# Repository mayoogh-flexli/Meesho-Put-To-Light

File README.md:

# PTL-RAIL — Meesho Put-To-Light IR Rail

Modular, daisy-chained **5-node IR emitter/receiver rail** for the Meesho
put-to-light system. Each 400 mm board has five bin positions on an 84 mm pitch.
Each position has an IR LED firing out of the top edge into the bin above and a
TSOP IR receiver looking out of the bottom edge into the bin below. An onboard
**ESP32-S3** drives the emitters, reads its own receivers and the receivers of
the board above, and talks to the rest of the system over **CAN**. Power, CAN
and the receiver signals pass from board to board through screw terminals.

| | |
|---|---|
| **Board** | PTL-RAIL |
| **Revision** | rev A (v1.0) |
| **Status** | Released as [`ptl-rail-rev-a-v1.0`](../../releases/tag/ptl-rail-rev-a-v1.0). ERC/DRC clean; see [§14](#14-known-issues-rev-a) for open items |
| **EDA** | KiCad 10 |
| **License** | Private / Internal (Flexli Technologies) |

---

## 1. Overview

One board type, chained end to end along a rack:

- **IR emitter row (top edge):** 5× IR333C 5 mm IR LEDs (D7–D11), mounted horizontally so the lens points out of the top edge. Each LED is switched by an AO3400A low-side MOSFET (Q1–Q5) from an ESP32 GPIO (`TX_1`…`TX_5`).
- **IR receiver row (bottom edge):** 5× TSOP382xx (U6–U10), lens pointing out of the bottom edge. Their outputs (`TSOP_OUT_1`…`5`) leave on **J3** to the board below. The receivers of the board above arrive on **J4** (`TSOP_OUT_n_ESP`) and go into the ESP32.
- **3D-printed shrouds:** each LED and each TSOP sits under a printed shroud (28 mm silk outline), held by two M3 screws, which reduces reflections and narrows the field of view.
- **Controller:** ESP32-S3-WROOM-1 (native USB through J1, onboard antenna overhanging the top edge), WS2812B status LEDs, RST/BOOT buttons and a user ACK button.
- **Bus and power:** CAN via SN65HVD230 with PESD1CAN ESD and switchable 120 Ω termination. VIN (24 V nominal) → TPS54360B buck → +5 V → TLV1117-33 → +3V3.

---

## 2. Architecture Block Diagram

```mermaid
flowchart TB
    subgraph PWR["Power"]
        VIN[("VIN 24 V nominal\nJ3/J4/J5/J6")] --> BUCK["TPS54360B buck\n(L1 15 uH, D1 SS36) -> +5V"]
        BUCK --> LDO["TLV1117-33\nLDO -> +3V3"]
        USB[("J1 USB 5V")] -->|"D3 SS14"| BUCK5(("+5V"))
    end

    subgraph MCU["Controller"]
        ESP["ESP32-S3-WROOM-1"]
        CAN["SN65HVD230 + PESD1CAN\nSW3 120R termination"]
        RGB["WS2812B x3 (D4-D6)"]
        ESP -->|"IO15/IO16"| CAN
        ESP -->|"IO18"| RGB
    end

    subgraph NODES["5 nodes, 84 mm pitch"]
        TX["5x IR333C + AO3400A\n(top edge)"]
        RX["5x TSOP382xx\n(bottom edge)"]
    end

    ESP -->|"TX_1-5 (IO9-IO13)"| TX
    RX -->|"TSOP_OUT_1-5 -> J3"| BELOW(["board below"])
    ABOVE(["board above"]) -->|"J4 -> IO4-IO8"| ESP
    CAN <-->|"CAN_H/CAN_L\nJ5/J6, J3/J4"| BUS(["CAN bus"])
```

---

## 3. Board Snapshots

### Top

### Bottom (node passives and MOSFETs)

### Node 2, ESP32, USB and CAN close-up

---

## 4. Features

| | |
|---|---|
| Board | 400 × 40 mm, 2-layer FR-4, 1.6 mm. 4 mm corner radius, concentric with the corner holes |
| Nodes | 5. Centres at x = 32, 116, 200, 284, 368 mm from the left edge |
| Emitters | IR333C, 180 Ω from +5 V, AO3400A low-side switch, 100 Ω gate resistor and 100 kΩ pull-down |
| Receivers | TSOP382xx on +3V3 through 100 Ω + 4.7 µF, 100 Ω series resistor on the output |
| Controller | ESP32-S3-WROOM-1, native USB (USBLC6-2 ESD) on J1 |
| Bus | CAN, SN65HVD230, PESD1CAN, switchable 120 Ω termination (SW3 + R7) |
| User I/O | SW1 RST, SW2 BOOT, SW4 ACK_BUTTON (IO14, 10 kΩ pull-up, 100 nF), D2 power LED, D4–D6 WS2812B |
| Copper | GND pour on both layers, redundant GND vias, GND via fence along the board edge |
| Test | TP1–TP19 (loop test points on every TX/RX signal and every rail, see [§10](#10-test-points)) |

---

## 5. Absolute Maximum Ratings

Stress ratings come from the component datasheets. **Rev A has no input protection** (see [§14](#14-known-issues-rev-a)), so these are the limits of the silicon itself.

| Parameter | Limiting part | Min | Max | Unit |
|---|---|---:|---:|---|
| `VIN` | TPS54360B (U2) | −0.3 | 65 | V |
| `VIN` on C1/C3 | capacitor rating, not yet specified | — | rating TBD | V |
| CAN_H / CAN_L bus pins | SN65HVD230 (U5) | −4 | 16 | V |
| +3V3 rail | ESP32-S3 / TLV1117 output | −0.3 | 3.6 | V |
| +5V rail | USBLC6-2 VBUS (U4) | −0.3 | 5.5 | V |

## 6. Recommended Operating Conditions

| Parameter | Min | Typ | Max | Unit |
|---|---:|---:|---:|---|
| `VIN` | 4.5 (U2) | 24 | 60 (U2), subject to C1/C3 rating | V |
| CAN data rate | — | — | 1 | Mbps |

---

## 7. System Wiring Diagram

```mermaid
flowchart TB
    A["Rail board N-1 (above)"] -->|"J3 -> J4\nTSOP_OUT 1-5, CAN, VIN, GND"| B["Rail board N"]
    B -->|"J3 -> J4"| C["Rail board N+1 (below)"]
    L(["neighbour on the left"]) <-->|"J5: CAN_H, CAN_L, VIN, GND"| B
    B <-->|"J6: GND, VIN, CAN_L, CAN_H"| R(["neighbour on the right"])
```

J3 carries this board's receiver outputs down to the next board's J4, which
feeds that board's ESP32 IO4–IO8. J3/J4 also pass CAN and power. J5/J6 at the
two ends of the board are mirrored 4-way CAN + power terminals for chaining
along the rail. The J3 → J4 pin order is reversed (J3.1 = RX1, J4.10 = RX1), so
**check the harness before first power-up**.

---

## 8. Connector Reference

Pin labels are printed on both silkscreen sides.

| Connector | Type | Pinout (1→N) |
|---|---|---|
| `J3` TSOP OUT | 10-way 3.5 mm screw terminal | 1–5: `RX1`…`RX5` (TSOP_OUT_1…5) · 6: `CAN_H` · 7: `CAN_L` · 8: `VIN` · 9: `GND` · 10: `GND` |
| `J4` TSOP IN | 10-way 3.5 mm screw terminal | 1: `GND` · 2: `GND` · 3: `VIN` · 4: `CAN_L` · 5: `CAN_H` · 6–10: `RX5`…`RX1` (TSOP_OUT_5…1_ESP) |
| `J5` (left end) | 4-way 3.5 mm screw terminal | 1: `CAN_H` · 2: `CAN_L` · 3: `VIN` · 4: `GND` |
| `J6` (right end) | 4-way 3.5 mm screw terminal | 1: `GND` · 2: `VIN` · 3: `CAN_L` · 4: `CAN_H` |
| `J1` USB | JST-PH 4-way | 1: `GND` · 2: `D+` · 3: `D−` · 4: `5V` (VBUS, via D3) |
| `SW3` | slide DIP | ON = 120 Ω (R7) across CAN_H/CAN_L |

---

## 9. ESP32-S3-WROOM-1 Pin Allocation

| Pin # | Pin name | Net / function |
|---:|---|---|
| 1 | `GND` | Ground |
| 2 | `3V3` | 3.3 V supply |
| 3 | `EN` | `ESP_EN`, reset (SW1) |
| 4 | `IO4` | `TSOP_OUT_1_ESP` (J4.10) |
| 5 | `IO5` | `TSOP_OUT_2_ESP` (J4.9) |
| 6 | `IO6` | `TSOP_OUT_3_ESP` (J4.8) |
| 7 | `IO7` | `TSOP_OUT_4_ESP` (J4.7) |
| 8 | `IO15` | `CAN_TX` |
| 9 | `IO16` | `CAN_RX` |
| 10 | `IO17` | *unused* |
| 11 | `IO18` | `STATUS_LED` (WS2812B DIN, D4→D5→D6) |
| 12 | `IO8` | `TSOP_OUT_5_ESP` (J4.6) |
| 13 | `IO19` | `USB_D-` |
| 14 | `IO20` | `USB_D+` |
| 15 | `IO3` | *unused (strap pin)* |
| 16 | `IO46` | *unused (strap pin)* |
| 17 | `IO9` | `TX_1` (emitter node 1) |
| 18 | `IO10` | `TX_2` |
| 19 | `IO11` | `TX_3` |
| 20 | `IO12` | `TX_4` |
| 21 | `IO13` | `TX_5` |
| 22 | `IO14` | `ACK_BUTTON` (SW4) |
| 23–25 | `IO21`, `IO47`, `IO48` | *unused* |
| 26 | `IO45` | *unused, no-connect (VDD_SPI strap; keep low at boot)* |
| 27 | `IO0` | `GPIO0`, BOOT (SW2) |
| 28–35 | `IO35`–`IO42` | *unused* |
| 36, 37 | `RXD0`, `TXD0` | *unused (UART0 debug)* |
| 38, 39 | `IO2`, `IO1` | *unused (ADC-capable)* |
| 40, 41 | `GND` | Ground / thermal pad |

---

## 10. Test Points

| TP | Net | Footprint |
|---|---|---|
| TP1 / TP2 | `USBC_D+` / `USBC_D−` (connector side) | SMD pad Ø1.5 mm |
| TP3 / TP4 | `USB_D+` / `USB_D−` (ESP32 side) | SMD pad Ø1.5 mm |
| TP5 … TP9 | `TX_1` … `TX_5` | Loop Ø1.8 mm, drill 1.0 mm |
| TP10 … TP14 | `TSOP_OUT_1` … `TSOP_OUT_5` | Loop Ø1.8 mm, drill 1.0 mm |
| TP15 / TP16 / TP17 | `VIN` / `+5V` / `+3V3` | Loop Ø1.8 mm, drill 1.0 mm |
| TP18 / TP19 | `GND` | Loop Ø1.8 mm, drill 1.0 mm |

---

## 11. Mounting & IR Shrouds

- **Rail fixing:** H1–H4 (corners, M3 with plated pad, 4 mm from each edge) and H25–H28 (mid-board, M3 with plated pad).
- **Shroud fixing:** H5–H24 are NPTH Ø3.2 mm, at each node centre ±10 mm, 5.0 mm (LED side) and 35.0 mm (TSOP side) from the top edge. The 28 mm silk outlines show each shroud's footprint; no parts are placed inside them.
- **Antenna:** the ESP32 antenna overhangs the top edge by about 15 mm. Keep the rack upright and any metal clear of it.

---

## 12. Fabrication & Assembly

**Fabrication**
- 2-layer FR-4, 1.6 mm. Copper weight and surface finish are not specified in the design; 1 oz and HASL-LF or ENIG are suitable.
- Design rules: min track 0.2 mm, clearance 0.2 mm, via 0.6/0.3 mm, min hole 0.3 mm, copper-to-edge 0.5 mm, hole-to-hole 0.25 mm.
- U3's thermal-pad vias use 0.2 mm holes, below the 0.3 mm design rule. Confirm your fab can make them.
- **Panel:** 2-up, 400 × 127 mm. Board 2 is rotated 180° so both antenna overhangs land on the 20 mm top/bottom rails. Each long edge has 7 mouse-bite tabs (Ø0.5 mm, 0.8 mm pitch, 3 mm wide), placed clear of the LEDs, TSOPs, connectors and antenna. The rails carry 3 fiducials and 3 tooling holes.

**Assembly**
- **Top:** ESP32, power stage, CAN, WS2812Bs, switches, connectors, IR LEDs, TSOPs.
- **Bottom:** all node passives and MOSFETs (R9–R33, C22–C26, Q1–Q5).
- **Through-hole:** IR LEDs, TSOPs, screw terminals, J1, SW3 and the loop test points.

---

## 13. Releases

The production files are attached to each [GitHub release](../../releases). The current release is [`ptl-rail-rev-a-v1.0`](../../releases/tag/ptl-rail-rev-a-v1.0):

| Asset | File |
|---|---|
| Bill of Materials | `PTL-RAIL_revA_BOM.csv` (grouped by Value + Footprint; test points and holes excluded) |
| Gerbers + drill files (fabrication, 2-board panel) | `PTL-RAIL_revA_gerbers_drill_panel-2up.zip` (with panel pick-and-place in `assembly/`) |
| Interactive BOM | `PTL-RAIL_revA_ibom.html` |
| IPC netlist | `PTL-RAIL_revA_netlist.ipc` (IPC-D-356) |
| Pick-and-place position file | `PTL-RAIL_revA_pick-and-place.csv` (single board, both sides, mm) |
| Reference designator list | `PTL-RAIL_revA_refdes.csv` |
| Schematic (PDF plot) | `PTL-RAIL_revA_schematic.pdf` |
| Schematic (KiCad source) | `PTL-RAIL_revA_kicad-source.zip` (project, sheets, PCB, libraries, 3D models, panel PCB) |
| 3D model (STEP) | `PTL-RAIL_revA_step.zip` → `PTL-RAIL_revA.step` (board, components, copper, silkscreen; ~40 MB unzipped) |

### Repository layout

```
.
├── README.md                      This file
└── PTL-RAIL/
    ├── PTL-RAIL.kicad_pro         KiCad project
    ├── PTL-RAIL.kicad_sch         Root sheet
    ├── PTL-RAIL.kicad_pcb         Board layout
    ├── esp32.kicad_sch            ESP32-S3, USB, buttons, status LEDs, test points
    ├── power.kicad_sch            TPS54360B buck, TLV1117 LDO
    ├── can.kicad_sch              SN65HVD230 CAN interface
    ├── connectors.kicad_sch       J3/J4/J5/J6
    ├── tx_nodes.kicad_sch         5x IR emitter + MOSFET
    ├── rx_nodes.kicad_sch         5x TSOP receiver
    ├── lib/                       Project symbols, footprints (0_IC) and 3D models
    └── Docs/
        ├── datasheets/            Component datasheets
        └── renders/               Board renders used in this README
```

---

## 14. Known Issues (rev A)

1. **No 24 V input protection.** VIN goes straight to C1/C3 and U2: no fuse, reverse-polarity protection, TVS or bulk capacitor.
2. **CAN_L sits next to VIN** on J3 (7/8), J4 (3/4), J5 (2/3) and J6 (2/3). The SN65HVD230 bus pins are rated −4 … +16 V, so a 24 V short destroys the transceiver. Either separate the pins with GND or use a ±58/70 V part (e.g. TCAN1042, MCP2562FD).
3. **J3/J4 pin order is reversed.** Check the board-to-board harness.
4. **J4 inputs are unprotected.** IO4–IO8 connect straight to an off-board connector with no series resistor, pull-up, RC filter or ESD protection.
5. **WS2812B data level.** It is driven at 3.3 V while the LEDs run on 5 V (V_IH = 0.7 × VDD), which is marginal.
6. **No capacitor voltage ratings or MPNs.** C1/C3 sit on 24 V and need ≥ 50 V.
7. **U3 overlaps the node-3 emitter shroud and hole H19** (DRC exclusion set).
8. **J3–J6 3D models** are a Phoenix PT 3.5 mm stand-in (KiCad has no 4Ucon models). This affects renders only.

---

## 15. Revision History

| Revision | Date | Notes |
|---|---|---|
| rev A scaffold | 2026-10-17 | KiCad project skeleton: outline, holes, node markers, sheets. |
| rev A placement | 2026-10-17 | LED row on the top edge, TSOP row on the bottom edge, node parts at 84 mm pitch, J3/J4 10-way and J5/J6 4-way terminals, CAN block, buttons, status LEDs, mounting holes. |
| rev A layout | 2026-10-18 | IR shroud outlines and holes, node parts moved to the bottom side, routing with filleted bus, GND vias and edge via fence, silkscreen cleanup, mid-board holes, rounded corners, test points TP5–TP19, SW4 ACK button on IO14. |
| **rev A v1.0** | 2026-10-18 | Values normalised, ERC/DRC clean, 3D models, production files and release [`ptl-rail-rev-a-v1.0`](../../releases/tag/ptl-rail-rev-a-v1.0). |

---

© Flexli Technologies. Private / internal.

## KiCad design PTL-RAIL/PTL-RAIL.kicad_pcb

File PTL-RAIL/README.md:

# PTL-RAIL — modular IR TX/RX rail, rev A

KiCad 10 project for the Meesho put-to-light rail. One board carries five IR
emitter/receiver nodes, an ESP32-S3 controller and a CAN interface. Boards
daisy-chain through screw terminals.

| | |
|---|---|
| Board size | 400 × 40 mm, 4 mm corner radius (concentric with the corner holes) |
| Layers | 2 (F.Cu / B.Cu), 1.6 mm, GND pour on both layers with edge via fence |
| Nodes | 5, on an 84 mm pitch (centres at x = 32, 116, 200, 284, 368 mm from the left edge) |
| Controller | ESP32-S3-WROOM-1 (U3, onboard antenna, overhangs the top edge) |
| Bus | CAN, SN65HVD230 (U5) with PESD1CAN (CR1) and switchable 120 Ω termination (SW3 + R7) |
| Power | VIN (24 V nominal) → TPS54360B buck (U2, L1 15 µH, D1 SS36) → +5 V → TLV1117-33 (U1) → +3V3 |
| USB | J1 JST-PH 4-pin (5 V via D3 SS14, USBLC6-2 ESD on D+/D−) |

## Block overview

- **IR emitter row (top edge):** D7–D11 IR333C, 5 mm, mounted horizontally and firing out of the top edge. Each LED is switched by an AO3400A low-side MOSFET (Q1–Q5) with a 100 Ω gate resistor, a 100 kΩ gate pull-down and a 180 Ω LED resistor from +5 V.
- **IR receiver row (bottom edge):** U6–U10 TSOP382xx, lens facing out of the bottom edge. Each has a 100 Ω supply resistor and 4.7 µF on Vs (+3V3), plus a 100 Ω series resistor on the output.
- **Shrouds:** each emitter and each TSOP sits under a 3D-printed shroud (28 mm silk outline). Each shroud is held by two M3 screws at the node centre ±10 mm, which reduces reflections and narrows the field of view.
- **Status:** D4–D6 WS2812B chain on IO18; D2 power LED.
- **User inputs:** SW1 = RST (EN), SW2 = BOOT (IO0), SW4 = ACK_BUTTON (IO14, 10 kΩ pull-up R34, 100 nF C27).

## Connector pinouts

Pin labels are printed on both silkscreen sides.

**J3 — 10-way, TSOP OUT (towards the board below)**

| Pin | 1 | 2 | 3 | 4 | 5 | 6 | 7 | 8 | 9 | 10 |
|---|---|---|---|---|---|---|---|---|---|---|
| Signal | RX1 | RX2 | RX3 | RX4 | RX5 | CAN_H | CAN_L | VIN | GND | GND |

**J4 — 10-way, TSOP IN (from the board above, into the ESP32)**

| Pin | 1 | 2 | 3 | 4 | 5 | 6 | 7 | 8 | 9 | 10 |
|---|---|---|---|---|---|---|---|---|---|---|
| Signal | GND | GND | VIN | CAN_L | CAN_H | RX5 | RX4 | RX3 | RX2 | RX1 |

On J3, RXn is this board's TSOP output (TSOP_OUT_n). On J4, RXn is TSOP_OUT_n_ESP.

**J5 (left end) / J6 (right end) — 4-way CAN + power, mirrored**

| Pin | 1 | 2 | 3 | 4 |
|---|---|---|---|---|
| J5 | CAN_H | CAN_L | VIN | GND |
| J6 | GND | VIN | CAN_L | CAN_H |

**J1 — JST-PH 4-way USB:** 1 GND, 2 D+, 3 D−, 4 5 V (VBUS, via D3).

## ESP32-S3 pin map (U3)

| Function | GPIO | Module pin |
|---|---|---|
| TX_1 … TX_5 (emitter gates) | IO9 … IO13 | 17 … 21 |
| TSOP_OUT_1 … 5 _ESP (from J4) | IO4, IO5, IO6, IO7, IO8 | 4, 5, 6, 7, 12 |
| CAN_TX / CAN_RX | IO15 / IO16 | 8 / 9 |
| STATUS_LED (WS2812B DIN) | IO18 | 11 |
| ACK_BUTTON (SW4) | IO14 | 22 |
| USB D− / D+ | IO19 / IO20 | 13 / 14 |
| BOOT (SW2) | IO0 | 27 |
| EN (SW1) | EN | 3 |

All other GPIOs are unconnected. IO45 has a no-connect flag.

## Test points

| TP | Net | Footprint |
|---|---|---|
| TP1 / TP2 | USBC_D+ / USBC_D− (connector side) | Pad Ø1.5 mm |
| TP3 / TP4 | USB_D+ / USB_D− (ESP32 side) | Pad Ø1.5 mm |
| TP5 … TP9 | TX_1 … TX_5 | Loop Ø1.8 mm, drill 1.0 mm |
| TP10 … TP14 | TSOP_OUT_1 … TSOP_OUT_5 | Loop Ø1.8 mm, drill 1.0 mm |
| TP15 / TP16 / TP17 | VIN / +5V / +3V3 | Loop Ø1.8 mm, drill 1.0 mm |
| TP18 / TP19 | GND | Loop Ø1.8 mm, drill 1.0 mm |

## Mounting

- **Rail fixing:** H1–H4 (corners, M3 with plated pad, 4 mm from each edge), plus H25–H28 mid-board (M3 with plated pad).
- **Shroud fixing:** H5–H24 are NPTH Ø3.2 mm. They sit at each node centre ±10 mm, at y = 5.0 mm (LED side) and 35.0 mm (TSOP side) from the top edge.
- **Antenna:** the ESP32 antenna overhangs the top edge. Keep the rack upright and any metal clear of it.

## Fabrication notes

- 2-layer FR-4, 1.6 mm. Copper weight and surface finish are not specified in the design; 1 oz and HASL-LF or ENIG are suitable.
- Design rules: min track 0.2 mm, min clearance 0.2 mm, via 0.6 mm / 0.3 mm drill, min hole 0.3 mm, copper-to-edge 0.5 mm, hole-to-hole 0.25 mm.
- Some footprints (the U3 thermal pad vias) use 0.2 mm holes, below the 0.3 mm design minimum. That DRC check is set to ignore, so confirm your fab supports it.
- **Panel:** 2-up, 400 × 127 mm. Board 2 is rotated 180° so both antenna overhangs land on the 20 mm top/bottom rails. Boards are joined by 7 mouse-bite tabs per long edge (Ø0.5 mm, 0.8 mm pitch, 3 mm wide), placed clear of the LEDs, TSOPs, connectors and antenna. The rails carry 3 fiducials and 3 tooling holes.

## Assembly notes

- **Top side:** ESP32, power stage, CAN, WS2812s, switches, connectors, IR LEDs and TSOPs.
- **Bottom side:** all node passives and MOSFETs (R9–R33, C22–C26, Q1–Q5).
- **Through-hole:** IR LEDs, TSOPs, screw terminals, J1, SW3 and the loop test points.

## Production files (release assets)

| File | Content |
|---|---|
| `PTL-RAIL_revA_BOM.csv` | BOM grouped by Value + Footprint (test points and holes excluded) |
| `PTL-RAIL_revA_gerbers_drill_panel-2up.zip` | Gerbers, Excellon drill (PTH/NPTH) and drill maps for the 2-up panel, plus `assembly/` panel pick-and-place |
| `PTL-RAIL_revA_ibom.html` | Interactive HTML BOM |
| `PTL-RAIL_revA_netlist.ipc` | IPC-D-356 netlist for bare-board test |
| `PTL-RAIL_revA_pick-and-place.csv` | Single-board pick-and-place, both sides, mm |
| `PTL-RAIL_revA_refdes.csv` | Reference designator list (value, footprint, side, X/Y, rotation) |
| `PTL-RAIL_revA_schematic.pdf` | Schematic, all sheets |
| `PTL-RAIL_revA_kicad-source.zip` | KiCad project, schematics, PCB, local libraries and the panel PCB |

## Known open issues (rev A)

1. **No 24 V input protection.** VIN goes straight to C1/C3 and U2: no fuse, reverse-polarity protection, TVS or bulk capacitor.
2. **CAN_L sits next to VIN** on J3 (7/8), J4 (3/4), J5 (2/3) and J6 (2/3). The SN65HVD230 bus pins are rated −4 … +16 V, so a 24 V short destroys the transceiver. Either separate the pins with GND or use a ±58/70 V part (e.g. TCAN1042, MCP2562FD).
3. **J3/J4 pin order is reversed** (J3.1 = RX1, J4.10 = RX1). Check the harness wiring between boards.
4. **J4 inputs are unprotected.** IO4–IO8 connect straight to an off-board connector with no series resistor, pull-up, RC filter or ESD protection.
5. **WS2812B data level.** It is driven at 3.3 V while the LEDs run on 5 V (V_IH = 0.7 × VDD), which is marginal. Add a level shifter or a diode drop on the LED supply.
6. **No capacitor voltage ratings.** C1/C3 (on 24 V) need ≥ 50 V. No MPNs are assigned yet.
7. **U3 overlaps the node-3 emitter shroud and hole H19** (DRC exclusion set). The shroud screw lands near the module corner.

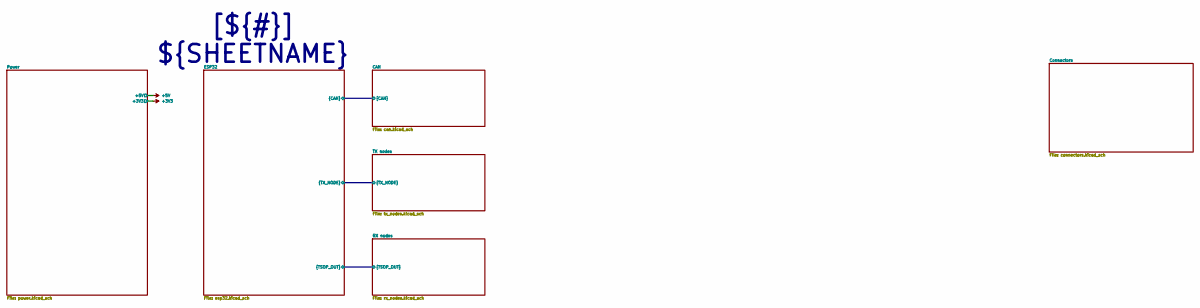
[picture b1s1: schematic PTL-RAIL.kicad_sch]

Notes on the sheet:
[${#}] ${SHEETNAME}

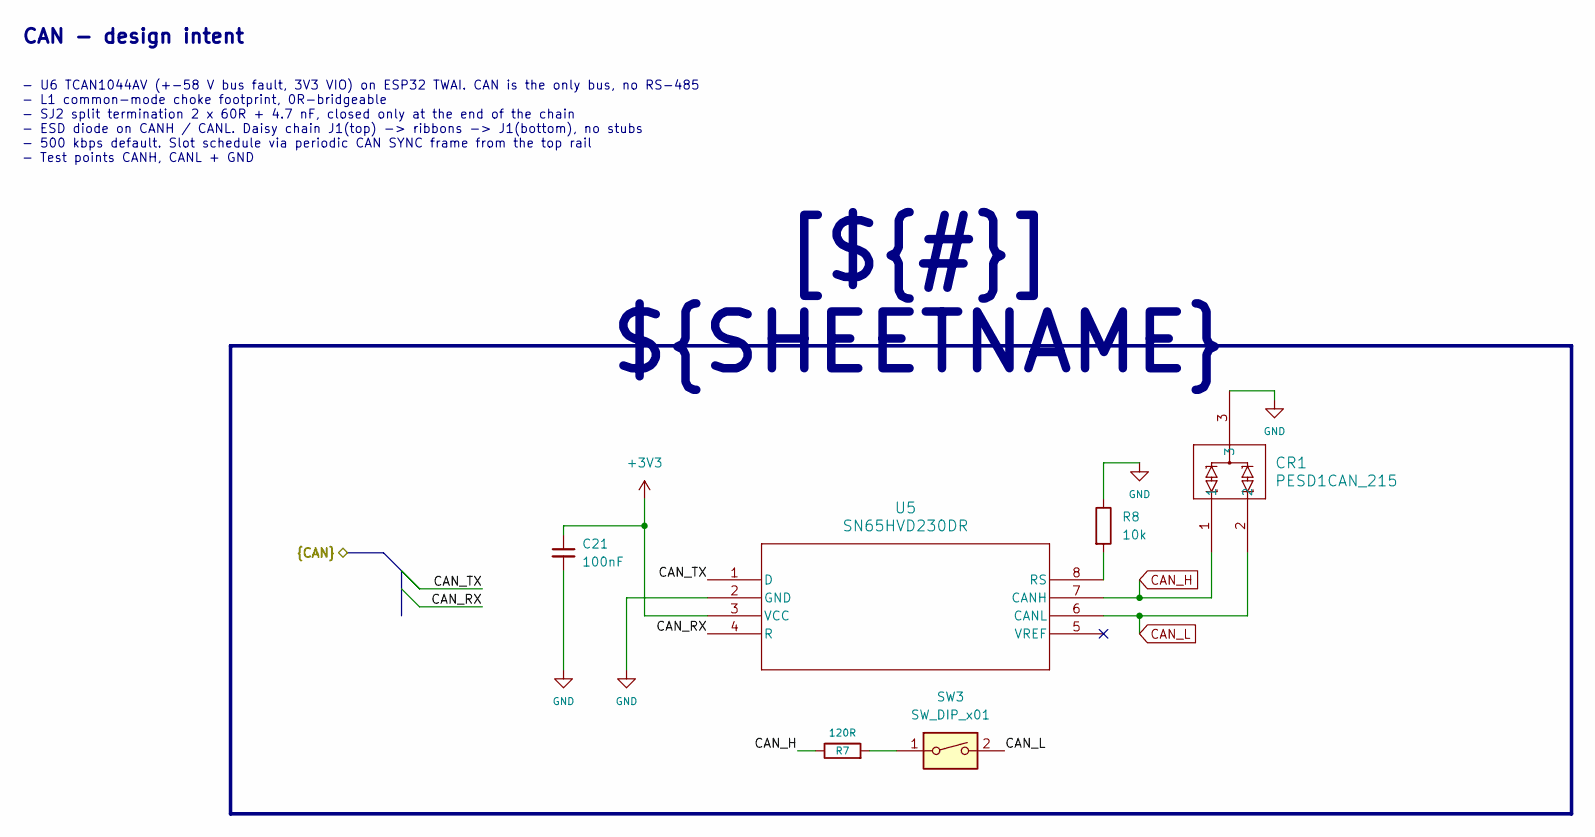
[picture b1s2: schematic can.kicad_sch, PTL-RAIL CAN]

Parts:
C21: 100nF; C_0805_2012Metric
CR1: PESD1CAN_215; SOT-23
R7: 120R; R_0805_2012Metric
R8: 10k; R_0805_2012Metric
SW3: SW_DIP_x01; SW_DIP_SPSTx01_Slide_9.78x4.72mm_W7.62mm_P2.54mm
U5: SN65HVD230DR; SOIC-8_3.9x4.9mm_P1.27mm

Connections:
+3V3: C21.1, U5.3 (VCC); also elsewhere on the board
/CAN/CAN_RX: U5.4 (R); also elsewhere on the board
/CAN/CAN_TX: U5.1 (D); also elsewhere on the board
CAN_H: CR1.1, R7.1, U5.7 (CANH); also elsewhere on the board
CAN_L: CR1.2, SW3.2, U5.6 (CANL); also elsewhere on the board
GND: C21.2, CR1.3, R8.1, U5.2 (GND); also elsewhere on the board
unnamed: R7.2, SW3.1
unnamed: R8.2, U5.8 (RS)

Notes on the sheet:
CAN - design intent
- U6 TCAN1044AV (+-58 V bus fault, 3V3 VIO) on ESP32 TWAI. CAN is the only bus, no RS-485 - L1 common-mode choke footprint, 0R-bridgeable - SJ2 split termination 2 x 60R + 4.7 nF, closed only at the end of the chain - ESD diode on CANH / CANL. Daisy chain J1(top) -> ribbons -> J1(bottom), no stubs 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
[${#}] ${SHEETNAME}

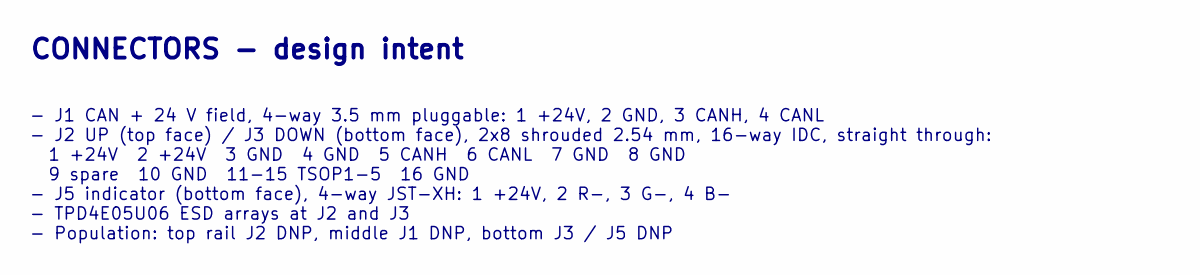
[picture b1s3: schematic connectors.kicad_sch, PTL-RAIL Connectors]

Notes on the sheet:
CONNECTORS - design intent
- J1 CAN + 24 V field, 4-way 3.5 mm pluggable: 1 +24V, 2 GND, 3 CANH, 4 CANL - J2 UP (top face) / J3 DOWN (bottom face), 2x8 shrouded 2.54 mm, 16-way IDC, straight through: 1 +24V 2 +24V 3 GND 4 GND 5 CANH 6 CANL 7 GND 8 GND 9 spare 10 GND 11-15 TSOP1-5 16 GND - J5 indicator (bottom face), 4-way JS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

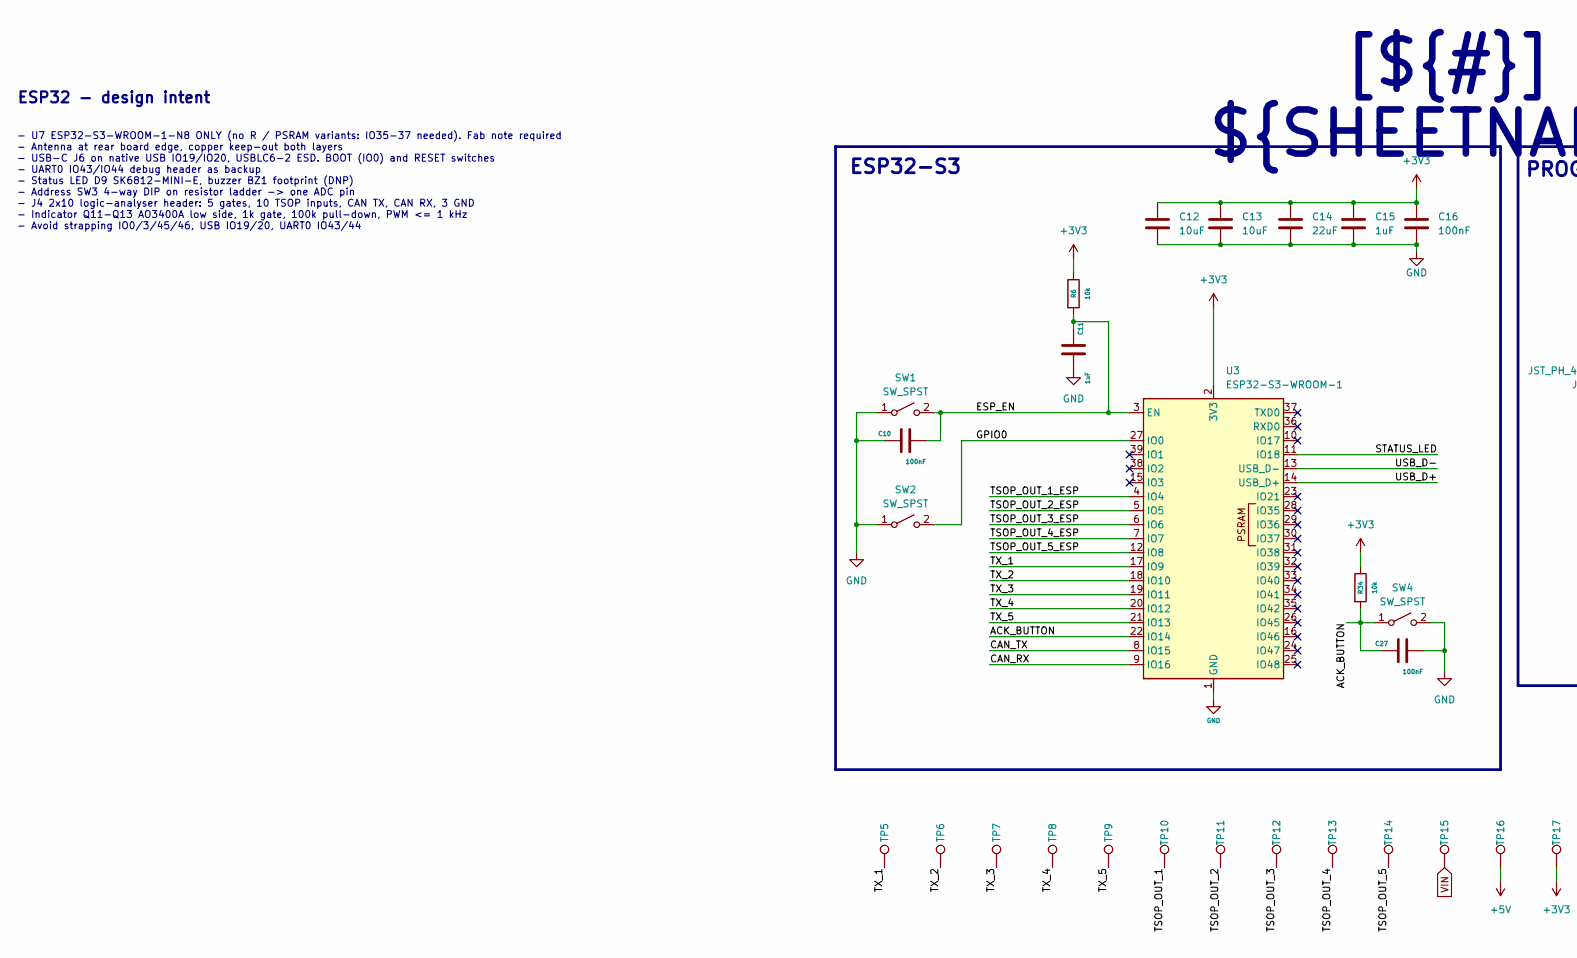
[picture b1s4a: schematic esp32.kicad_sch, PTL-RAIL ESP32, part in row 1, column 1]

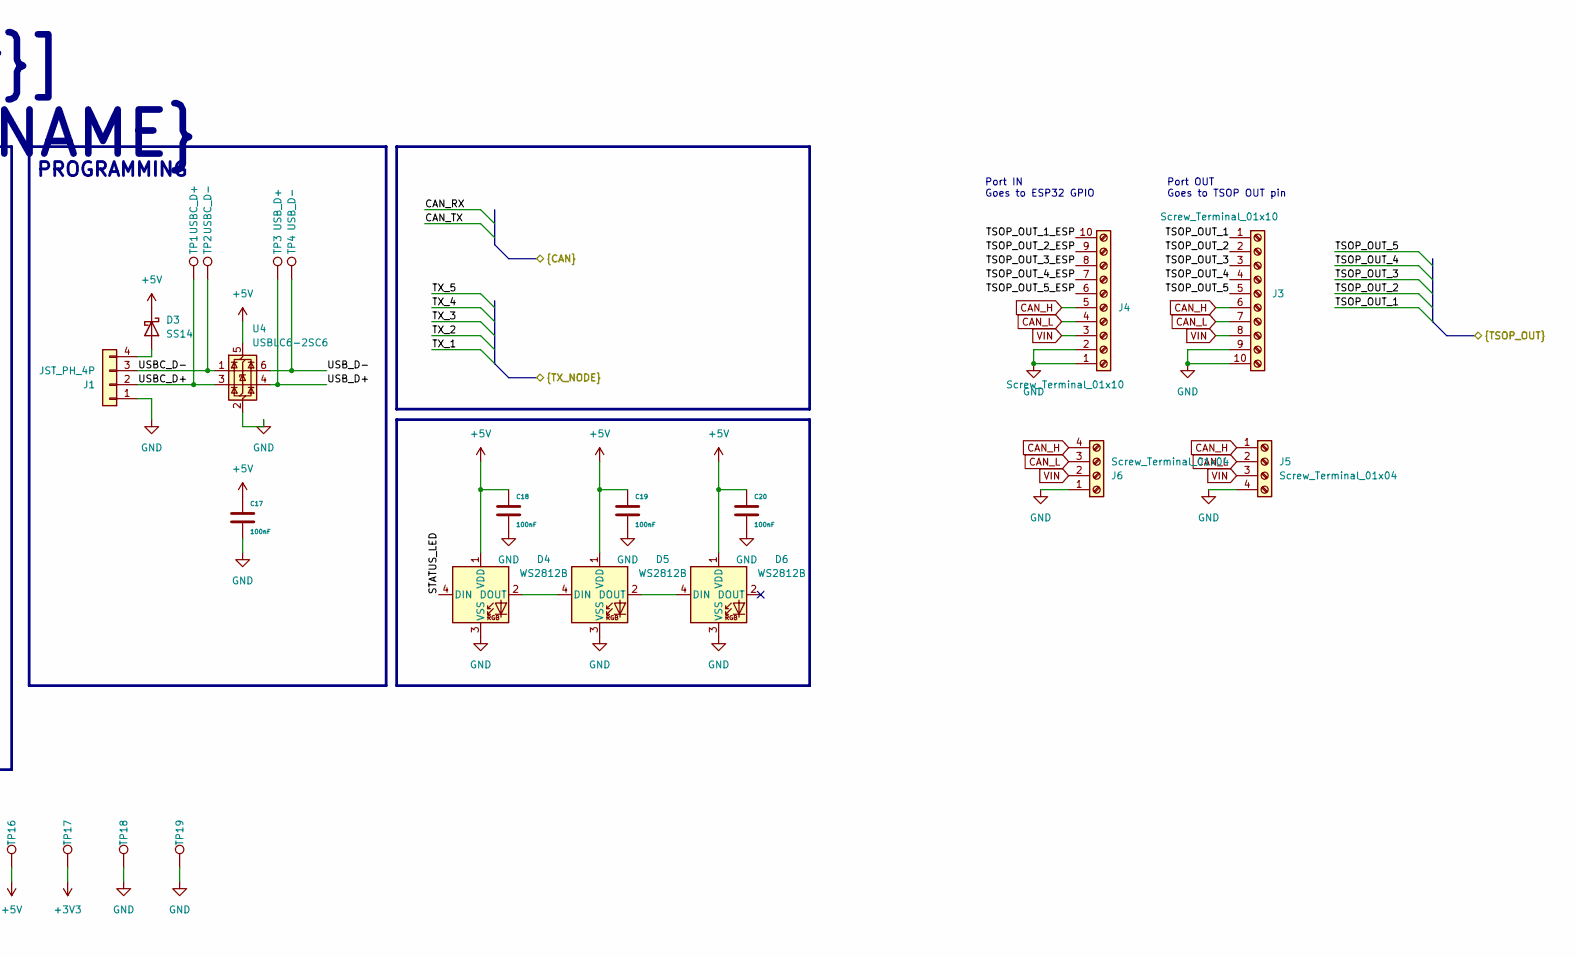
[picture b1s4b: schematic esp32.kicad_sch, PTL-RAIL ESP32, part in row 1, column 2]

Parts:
C10, C16, C17, C18, C19, C20, C27: 100nF; C_0805_2012Metric
C11, C15: 1uF; C_0805_2012Metric
C12, C13: 10uF; C_0805_2012Metric
C14: 22uF; C_0805_2012Metric
D3: SS14; D_SMA
D4, D5, D6: WS2812B; LED_WS2812B_PLCC4_5.0x5.0mm_P3.2mm
J1: JST_PH_4P; JST_PH_B4B-PH-K_1x04_P2.00mm_Vertical
J3, J4: Screw_Terminal_01x10; TerminalBlock_4Ucon_1x10_P3.50mm_Horizontal
J5, J6: Screw_Terminal_01x04; TerminalBlock_4Ucon_1x04_P3.50mm_Horizontal
R6, R34: 10k; R_0805_2012Metric
SW1, SW2, SW4: SW_SPST; SW_SPST_PTS645Sx43SMTR92
TP1: USBC_D+; TestPoint_Pad_D1.5mm
TP2: USBC_D-; TestPoint_Pad_D1.5mm
TP3: USB_D+; TestPoint_Pad_D1.5mm
TP4: USB_D-; TestPoint_Pad_D1.5mm
TP5: TX_1; TestPoint_Loop_D1.80mm_Drill1.0mm_Beaded
TP6: TX_2; TestPoint_Loop_D1.80mm_Drill1.0mm_Beaded
TP7: TX_3; TestPoint_Loop_D1.80mm_Drill1.0mm_Beaded
TP8: TX_4; TestPoint_Loop_D1.80mm_Drill1.0mm_Beaded
TP9: TX_5; TestPoint_Loop_D1.80mm_Drill1.0mm_Beaded
TP10: TSOP_OUT_1; TestPoint_Loop_D1.80mm_Drill1.0mm_Beaded
TP11: TSOP_OUT_2; TestPoint_Loop_D1.80mm_Drill1.0mm_Beaded
TP12: TSOP_OUT_3; TestPoint_Loop_D1.80mm_Drill1.0mm_Beaded
TP13: TSOP_OUT_4; TestPoint_Loop_D1.80mm_Drill1.0mm_Beaded
TP14: TSOP_OUT_5; TestPoint_Loop_D1.80mm_Drill1.0mm_Beaded
TP15: VIN; TestPoint_Loop_D1.80mm_Drill1.0mm_Beaded
TP16: +5V; TestPoint_Loop_D1.80mm_Drill1.0mm_Beaded
TP17: +3V3; TestPoint_Loop_D1.80mm_Drill1.0mm_Beaded
TP18, TP19: GND; TestPoint_Loop_D1.80mm_Drill1.0mm_Beaded
U3: ESP32-S3-WROOM-1
U4: USBLC6-2SC6; SOT-23-6

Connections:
+3V3: C12.1, C13.1, C14.1, C15.1, C16.1, R6.1, R34.1, TP17.1 (1_1), U3.2 (3V3); also elsewhere on the board
+5V: C17.1, C18.1, C19.1, C20.1, D3.1 (K), D4.1 (VDD), D5.1 (VDD), D6.1 (VDD), TP16.1 (1_1), U4.5 (VBUS); also elsewhere on the board
/CAN/CAN_RX: U3.9 (IO16); also elsewhere on the board
/CAN/CAN_TX: U3.8 (IO15); also elsewhere on the board
/ESP32/ACK_BUTTON: C27.1, R34.2, SW4.1 (A), U3.22 (IO14)
/ESP32/ESP_EN: C10.2, C11.1, R6.2, SW1.2 (B), U3.3 (EN)
/ESP32/GPIO0: SW2.2 (B), U3.27 (IO0)
/ESP32/STATUS_LED: D4.4 (DIN), U3.11 (IO18)
/ESP32/TSOP_OUT_1: J3.1, TP10.1 (1_1); also elsewhere on the board
/ESP32/TSOP_OUT_1_ESP: J4.10, U3.4 (IO4)
/ESP32/TSOP_OUT_2: J3.2, TP11.1 (1_1); also elsewhere on the board
/ESP32/TSOP_OUT_2_ESP: J4.9, U3.5 (IO5)
/ESP32/TSOP_OUT_3: J3.3, TP12.1 (1_1); also elsewhere on the board
/ESP32/TSOP_OUT_3_ESP: J4.8, U3.6 (IO6)
/ESP32/TSOP_OUT_4: J3.4, TP13.1 (1_1); also elsewhere on the board
/ESP32/TSOP_OUT_4_ESP: J4.7, U3.7 (IO7)
/ESP32/TSOP_OUT_5: J3.5, TP14.1 (1_1); also elsewhere on the board
/ESP32/TSOP_OUT_5_ESP: J4.6, U3.12 (IO8)
/ESP32/TX_1: TP5.1 (1_1), U3.17 (IO9); also elsewhere on the board
/ESP32/TX_2: TP6.1 (1_1), U3.18 (IO10); also elsewhere on the board
/ESP32/TX_3: TP7.1 (1_1), U3.19 (IO11); also elsewhere on the board
/ESP32/TX_4: TP8.1 (1_1), U3.20 (IO12); also elsewhere on the board
/ESP32/TX_5: TP9.1 (1_1), U3.21 (IO13); also elsewhere on the board
/ESP32/USBC_D+: J1.2, TP1.1 (1_1), U4.3 (I/O2)
/ESP32/USBC_D-: J1.3, TP2.1 (1_1), U4.1 (I/O1)
/ESP32/USB_D+: TP3.1 (1_1), U3.14 (USB_D+), U4.4 (I/O2)
/ESP32/USB_D-: TP4.1 (1_1), U3.13 (USB_D-), U4.6 (I/O1)
CAN_H: J3.6, J4.5, J5.1, J6.4; also elsewhere on the board
CAN_L: J3.7, J4.4, J5.2, J6.3; also elsewhere on the board
GND: C10.1, C11.2, C12.2, C13.2, C14.2, C15.2, C16.2, C17.2, C18.2, C19.2, C20.2, C27.2, D4.3 (VSS), D5.3 (VSS), D6.3 (VSS), J1.1, J3.9, J3.10, J4.1, J4.2, J5.4, J6.1, SW1.1 (A), SW2.1 (A), SW4.2 (B), TP18.1 (1_1), TP19.1 (1_1), U3.1 (GND), U3.40 (GND), U3.41 (GND), U4.2 (GND); also elsewhere on the board
unnamed: D3.2 (A), J1.4
unnamed: D4.2 (DOUT), D5.4 (DIN)
unnamed: D5.2 (DOUT), D6.4 (DIN)
VIN: J3.8, J4.3, J5.3, J6.2, TP15.1 (1_1); also elsewhere on the board

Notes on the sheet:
PROGRAMMING
- U7 ESP32-S3-WROOM-1-N8 ONLY (no R / PSRAM variants: IO35-37 needed). Fab note required - Antenna at rear board edge, copper keep-out both layers - USB-C J6 on native USB IO19/IO20, USBLC6-2 ESD. BOOT (IO0) and RESET switches - UART0 IO43/IO44 debug header as backup - Status LED D9 SK6812-MINI-E, 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
Port OUT Goes to TSOP OUT pin
ESP32-S3
ESP32 - design intent
Port IN Goes to ESP32 GPIO
[${#}] ${SHEETNAME}

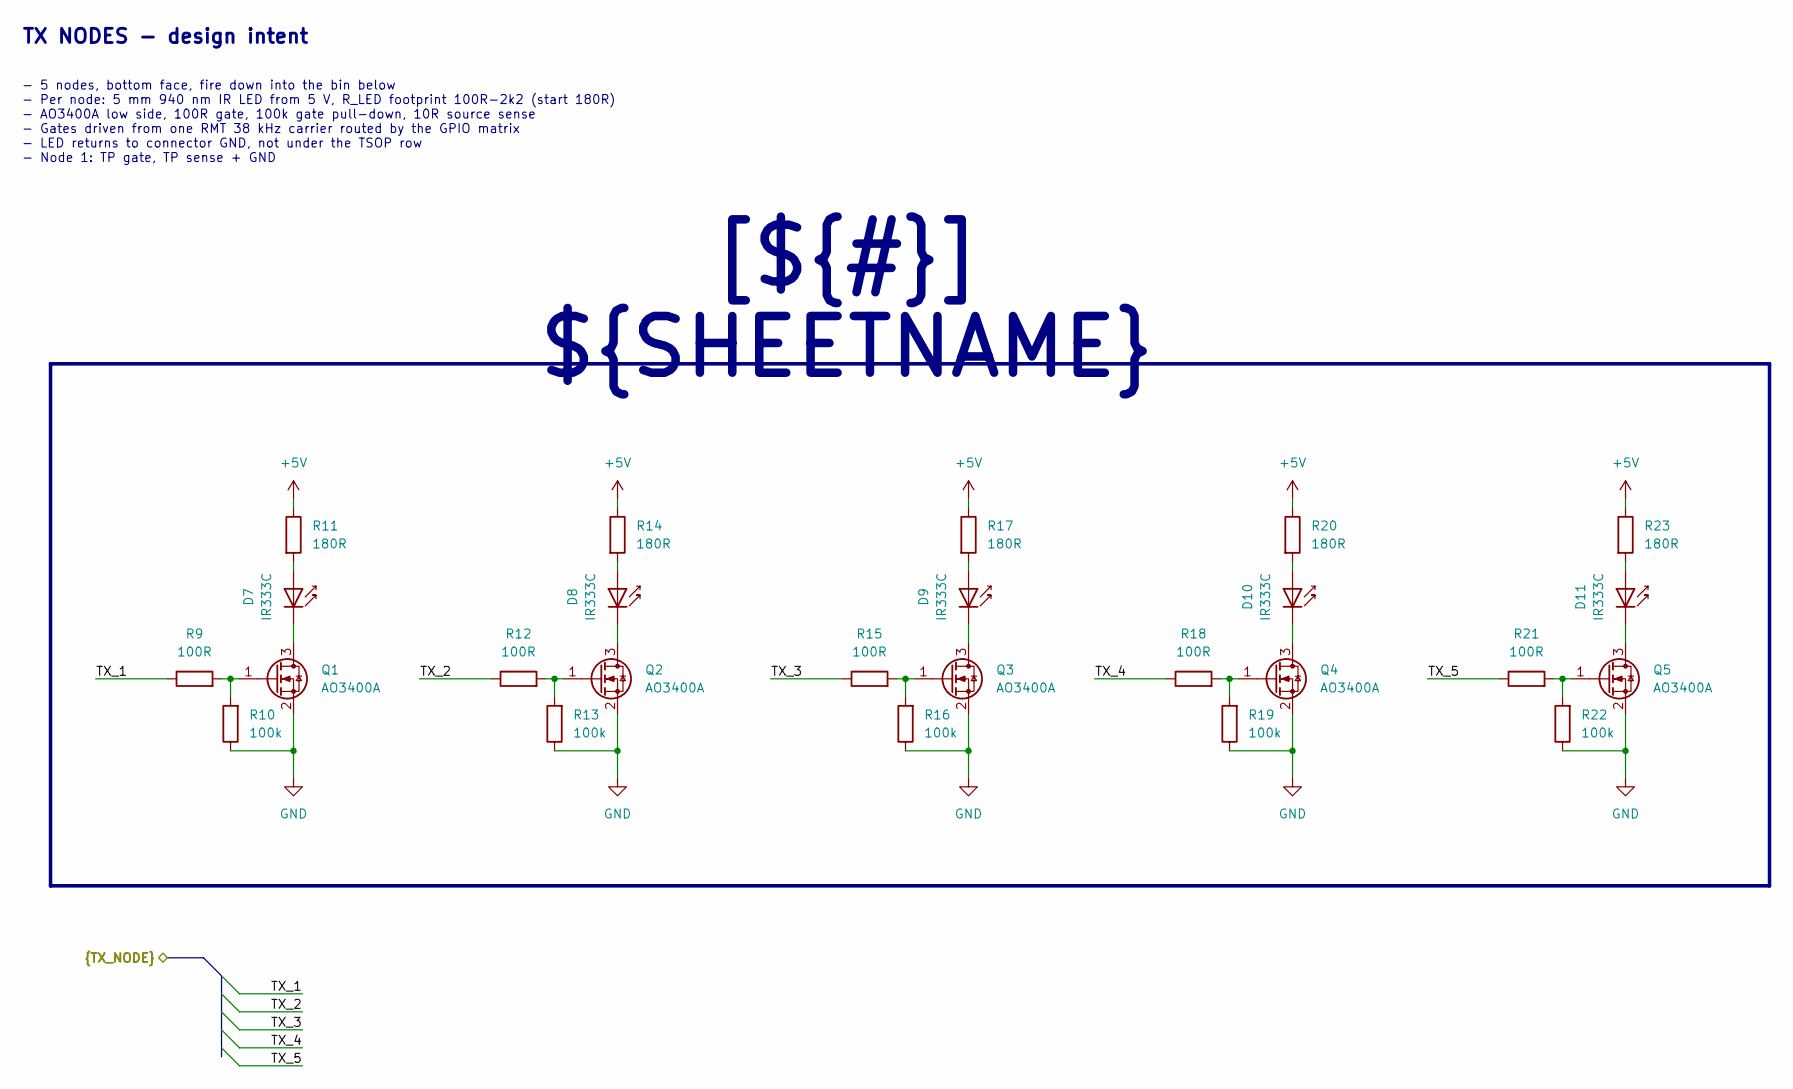
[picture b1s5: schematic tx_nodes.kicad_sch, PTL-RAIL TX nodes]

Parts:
D7, D8, D9, D10, D11: IR333C; LED_D5.0mm_Horizontal_O1.27mm_Z3.0mm_IRGrey
Q1, Q2, Q3, Q4, Q5: AO3400A; SOT-23
R9, R12, R15, R18, R21: 100R; R_0805_2012Metric
R10, R13, R16, R19, R22: 100k; R_0805_2012Metric
R11, R14, R17, R20, R23: 180R; R_0805_2012Metric

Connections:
+5V: R11.1, R14.1, R17.1, R20.1, R23.1; also elsewhere on the board
/ESP32/TX_1: R9.1; also elsewhere on the board
/ESP32/TX_2: R12.1; also elsewhere on the board
/ESP32/TX_3: R15.1; also elsewhere on the board
/ESP32/TX_4: R18.1; also elsewhere on the board
/ESP32/TX_5: R21.1; also elsewhere on the board
GND: Q1.2 (S), Q2.2 (S), Q3.2 (S), Q4.2 (S), Q5.2 (S), R10.1, R13.1, R16.1, R19.1, R22.1; also elsewhere on the board
unnamed: D7.2 (A), R11.2
unnamed: D7.1 (K), Q1.3 (D)
unnamed: D8.2 (A), R14.2
unnamed: D8.1 (K), Q2.3 (D)
unnamed: D9.2 (A), R17.2
unnamed: D9.1 (K), Q3.3 (D)
unnamed: D10.2 (A), R20.2
unnamed: D10.1 (K), Q4.3 (D)
unnamed: D11.2 (A), R23.2
unnamed: D11.1 (K), Q5.3 (D)
unnamed: Q1.1 (G), R9.2, R10.2
unnamed: Q2.1 (G), R12.2, R13.2
unnamed: Q3.1 (G), R15.2, R16.2
unnamed: Q4.1 (G), R18.2, R19.2
unnamed: Q5.1 (G), R21.2, R22.2

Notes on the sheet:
- 5 nodes, bottom face, fire down into the bin below - Per node: 5 mm 940 nm IR LED from 5 V, R_LED footprint 100R-2k2 (start 180R) - AO3400A low side, 100R gate, 100k gate pull-down, 10R source sense - Gates driven from one RMT 38 kHz carrier routed by the GPIO matrix - LED returns to connector GN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
TX NODES - design intent
[${#}] ${SHEETNAME}

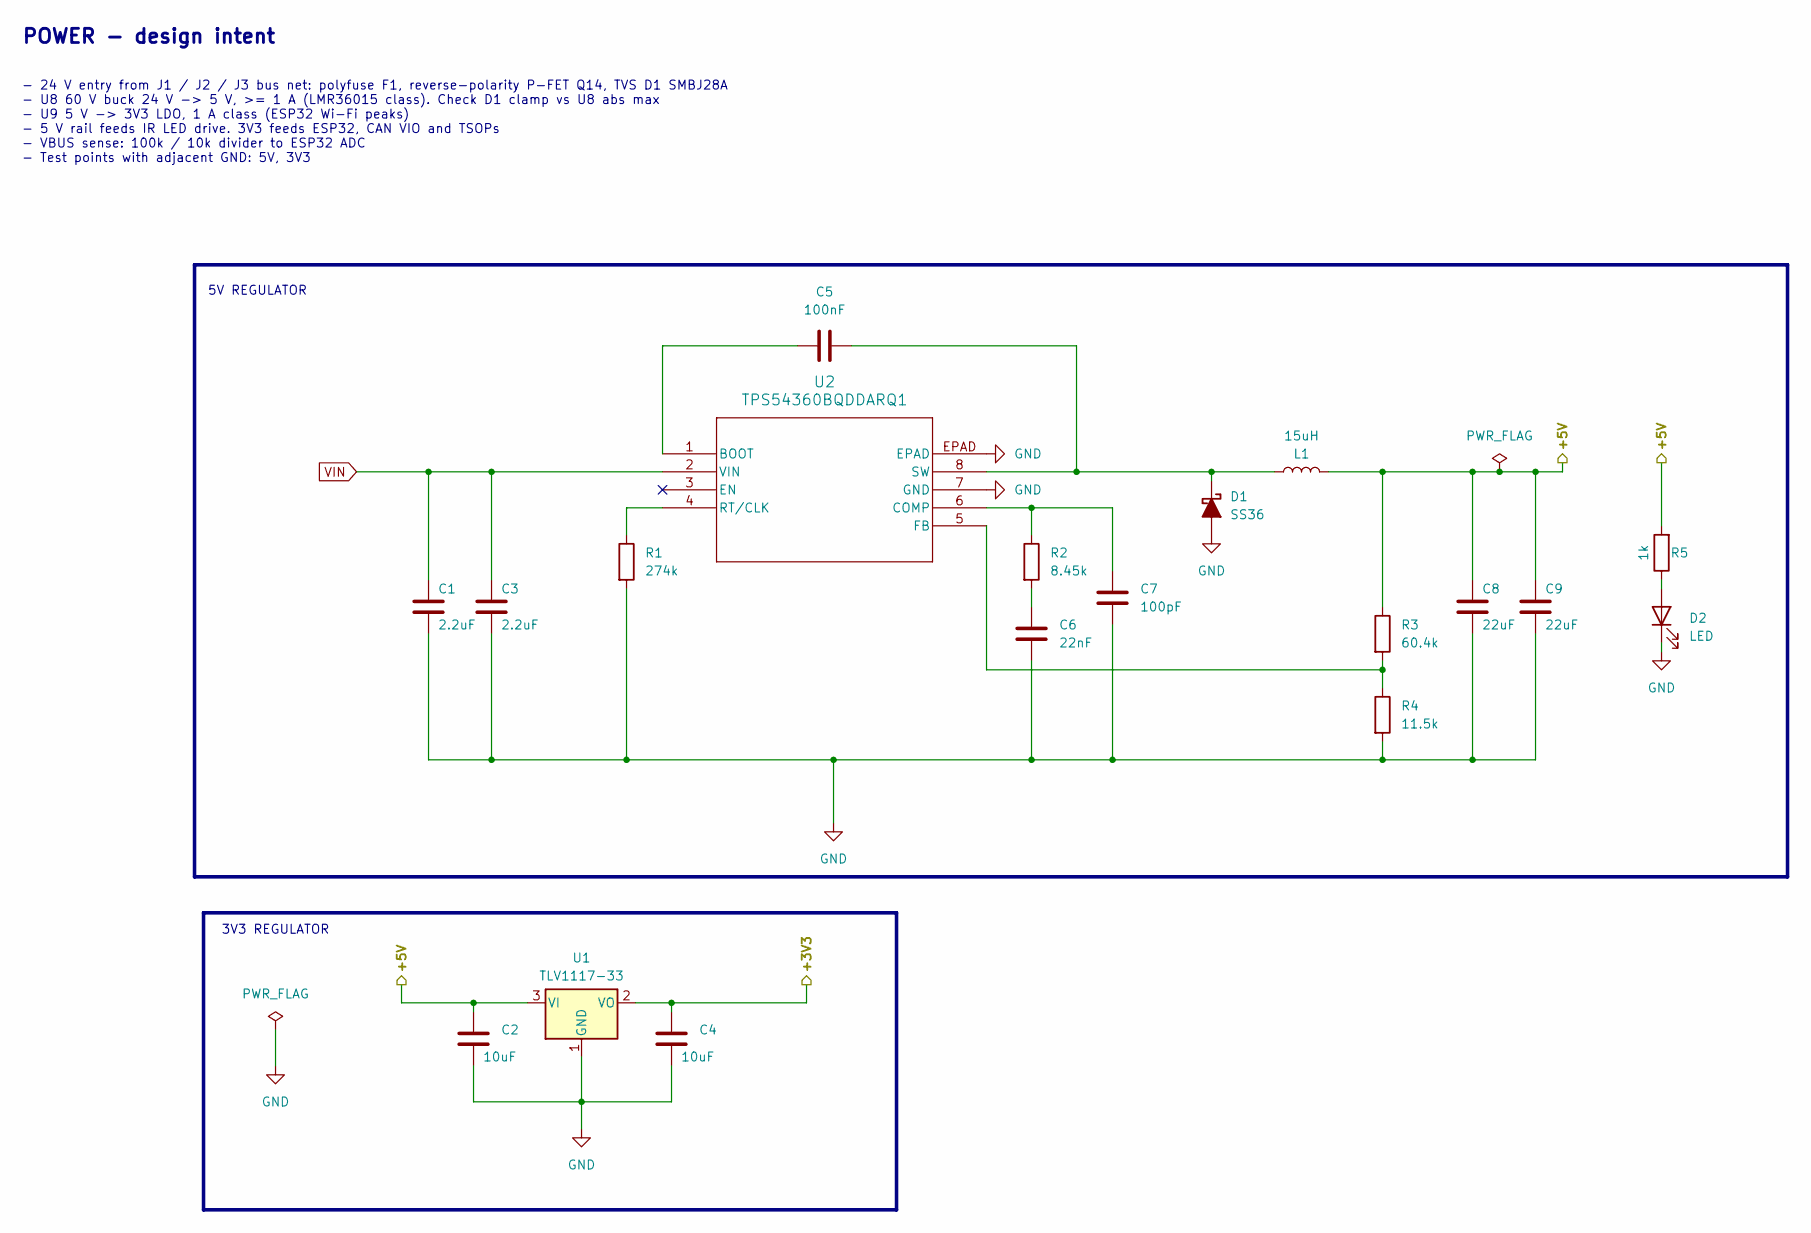
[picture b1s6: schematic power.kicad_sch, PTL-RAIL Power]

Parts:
C1, C3: 2.2uF; C_1210_3225Metric
C2, C4: 10uF; C_0805_2012Metric
C5: 100nF; C_0805_2012Metric
C6: 22nF; C_0805_2012Metric
C7: 100pF; C_0805_2012Metric
C8, C9: 22uF; C_1210_3225Metric
D1: SS36; D_SMC
D2: LED; LED_0805_2012Metric
L1: 15uH; L_APV_ANR8040
R1: 274k; R_0805_2012Metric
R2: 8.45k; R_0805_2012Metric
R3: 60.4k; R_0805_2012Metric
R4: 11.5k; R_0805_2012Metric
R5: 1k; R_0805_2012Metric
U1: TLV1117-33; SOT-223-3_TabPin2
U2: TPS54360BQDDARQ1

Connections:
+3V3: C4.1, U1.2 (VO); also elsewhere on the board
+5V: C2.1, C8.1, C9.1, L1.2, R3.1, R5.2, U1.3 (VI); also elsewhere on the board
GND: C1.2, C2.2, C3.2, C4.2, C6.2, C7.2, C8.2, C9.2, D1.2 (A), D2.1 (K), R1.2, R4.2, U1.1 (GND), U2.7 (GND), U2.EPAD; also elsewhere on the board
unnamed: C6.1, R2.2
unnamed: C5.2, D1.1 (K), L1.1, U2.8 (SW)
unnamed: D2.2 (A), R5.1
unnamed: C5.1, U2.1 (BOOT)
unnamed: C7.1, R2.1, U2.6 (COMP)
unnamed: R3.2, R4.1, U2.5 (FB)
unnamed: R1.1, U2.4 (RT/CLK)
VIN: C1.1, C3.1, U2.2 (VIN); also elsewhere on the board

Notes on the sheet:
POWER - design intent
3V3 REGULATOR
- 24 V entry from J1 / J2 / J3 bus net: polyfuse F1, reverse-polarity P-FET Q14, TVS D1 SMBJ28A - U8 60 V buck 24 V -> 5 V, >= 1 A (LMR36015 class). Check D1 clamp vs U8 abs max - U9 5 V -> 3V3 LDO, 1 A class (ESP32 Wi-Fi peaks) - 5 V rail feeds IR LED drive. 3V3 feeds ESP32, CAN VIO and TSOPs - VB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
5V REGULATOR
